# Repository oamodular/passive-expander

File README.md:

# Passive expander for Eurorack

It’s 4hp and has 7 patch cable sockets and 8 pins on the back. One for each of the 7, plus a pin for connecting a ground that is sent to each of the sockets. We found it useful in working on [Time Machine](https://github.com/oamodular/time-machine) but this is also a handy tool for bringing *any* expander pins to the front of your system.

On one side of the faceplate the sockets are number 1 through 7. On the other it has labels specific to Time Machine. Meep morp

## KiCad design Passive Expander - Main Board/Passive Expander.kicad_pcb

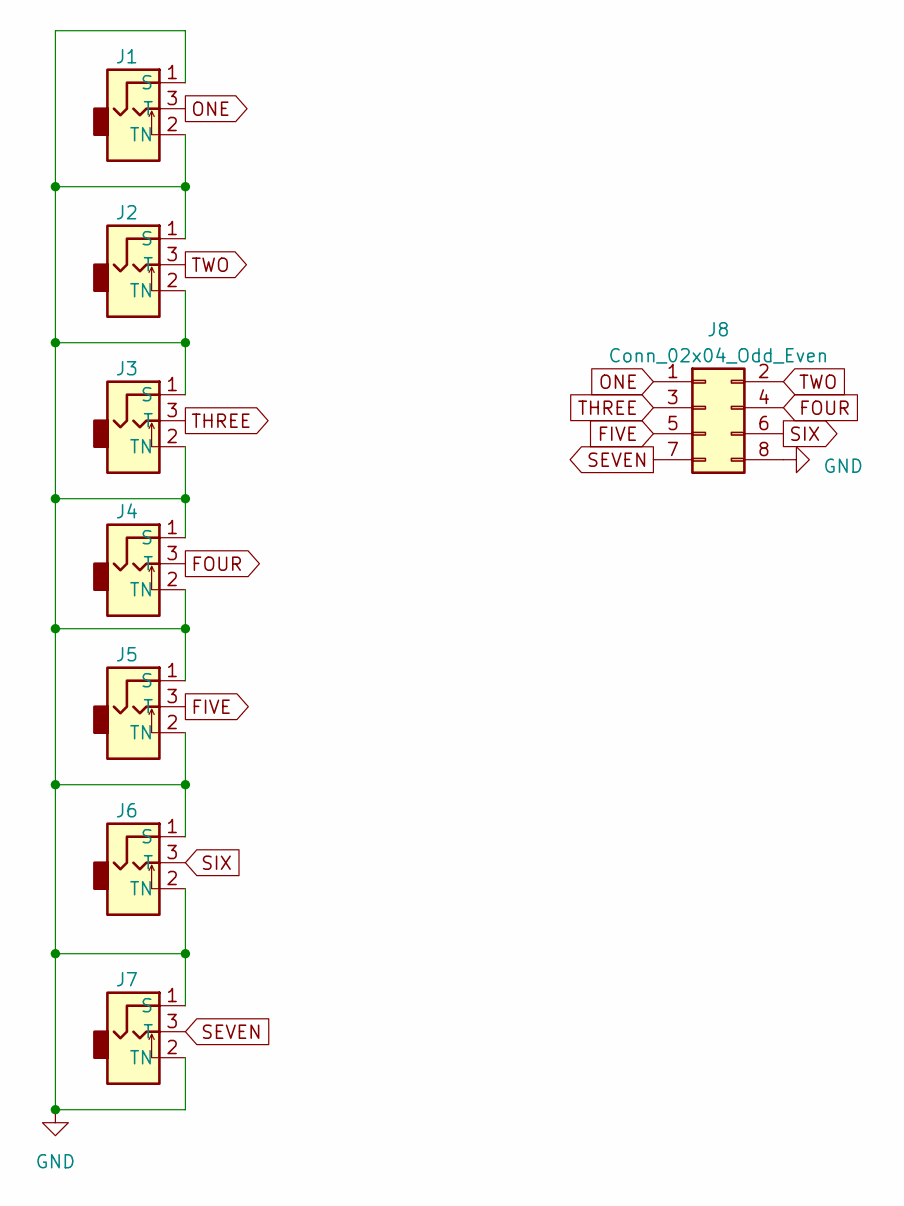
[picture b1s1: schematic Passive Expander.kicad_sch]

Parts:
J1, J2, J3, J4, J5, J6, J7: Socket-3.5mm THT-Thonkiconn PJ398SM-12
J8: Conn_02x04_Odd_Even; PinHeader_2x04_P2.54mm_Vertical

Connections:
FIVE: J5.3 (T), J8.5
FOUR: J4.3 (T), J8.4
GND: J1.1 (S), J1.2 (TN), J2.1 (S), J2.2 (TN), J3.1 (S), J3.2 (TN), J4.1 (S), J4.2 (TN), J5.1 (S), J5.2 (TN), J6.1 (S), J6.2 (TN), J7.1 (S), J7.2 (TN), J8.8
ONE: J1.3 (T), J8.1
SEVEN: J7.3 (T), J8.7
SIX: J6.3 (T), J8.6
THREE: J3.3 (T), J8.3
TWO: J2.3 (T), J8.2

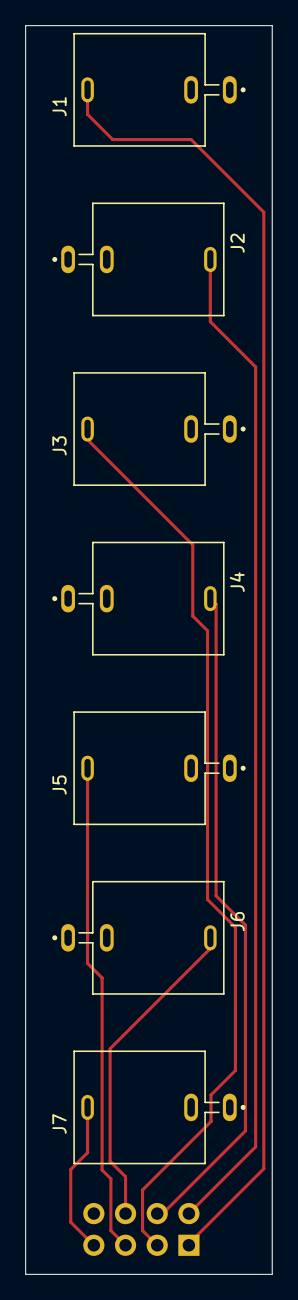
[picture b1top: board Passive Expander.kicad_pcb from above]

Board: 2 copper layers, 19.8 x 100.1 mm, 8 parts (1 on the bottom side), 8 nets.

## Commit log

2024-07-05 Create LICENSE.md
    BY-SA license from Creative Commons
2024-07-06 Update .gitignore for mac os
2024-07-06 adding the kicad shtuff
2024-07-06 some images for the readme that i haven't wrote yet
2024-07-06 i had to optimize the images. bad habits die hard
